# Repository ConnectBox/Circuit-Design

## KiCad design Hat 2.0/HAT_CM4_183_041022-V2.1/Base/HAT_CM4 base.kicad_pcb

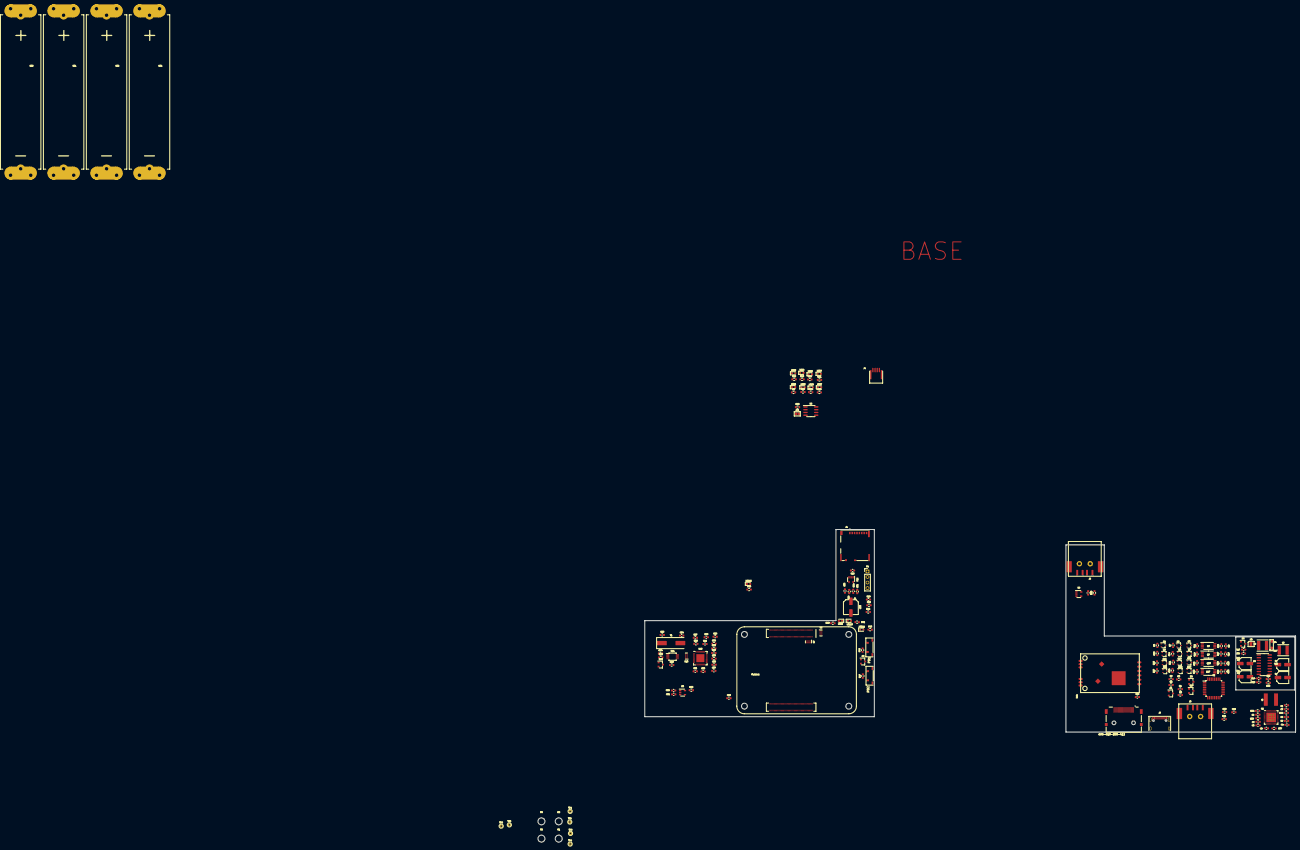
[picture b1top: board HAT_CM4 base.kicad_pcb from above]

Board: 2 copper layers, 299.3 x 93.1 mm, 178 parts (0 on the bottom side), 133 nets, no tracks yet.

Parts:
BT1, BT2, BT3, BT4: Battery Connector; Battery 18650-3
C1, C2, C3, C4, C19, C20, C25, C26, C27, C32, C34, C36, C38: 10uF; C_0603_1608Metric
C5, C6, C7: 4.7uF; C_0603_1608Metric
C8, C9, C18: 1uF; C_0603_1608Metric
C10, C39, C40: 22uF; C_0603_1608Metric
C11, C12, C16, C17: 150uf; CP_Elec_5x3
C13: 1.0uf; C_0603_1608Metric
C14: 0.22uf; C_0603_1608Metric
C15, C21, C22, C28, C29, C31, C33, C35, C37: 0.1uf; C_0603_1608Metric
C23, C24: 9pF; C_0603_1608Metric
C30: 100uF; CP_Elec_6.3x4.5
D1, D2, D3, D5: MMBD914; D_SOT-23_ANK
D4: NRVTS260ESFT1G; SOD-123FL
H1, H2, H3, H4: MountingHole; MountingHole_3.2mm_M3
J1: Micro_SD_Card; SDCARD_MOLEX_503398-1892
J2: 690-019-298-412; HDMI_CnC_SMT
J3, J5: USB_A; USB_A_CUI_smd
J4: Conn_01x04; HFW4R
J6: USB-C; USB-C-GCT
JP1: SolderJumper_2_Open; SolderJumper-2_P1.3mm_Open_TrianglePad1.0x1.5mm
L1: 4.7 uH; INDUCTOR_SMD_6x6-1
L2: 1.0 uH; L_Taiyo-Yuden_MD-5050
L3: 1.5 uH; L_Taiyo-Yuden_NR-50xx
LED1, LED3, LED5, LED7: Blue; LED_0603_1608Metric
LED2, LED4, LED6, LED8, LED9: Red; LED_0603_1608Metric
LED10: Green; LED_0603_1608Metric
LED11: LED Green; LED_0603_1608Metric
LED12: Amber; LED_0603_1608Metric
Module1: ComputeModule4; Raspberry-Pi-4-Compute-Module
P1: Conn_01x04; PinHeader_1x04_P2.54mm_Vertical
PB1, PB2: SPST-PUSH; SW-TL3330A
Q1: NX6008; SOT-23
Q2, Q3, Q4, Q6, Q7, Q8, Q10, Q11, Q12, Q14, Q15, Q16: 3J15; SOT-323_SC-70
Q5, Q9, Q13, Q17: 8205A; TSSOP-8_4.4x3mm_P0.65mm
Q18: 2N7002; SOT-23
R1, R6, R9, R13, R16, R20, R23, R27, R30, R35, R42, R46, R47: 10K; R_0603_1608Metric
R2, R43, R44, R54, R55: 2.2K; R_0603_1608Metric
R3, R4, R11, R18, R25, R33: 20K; R_0603_1608Metric
R5, R10, R14, R17, R21, R24, R28, R32: 100K; R_0603_1608Metric
R7: 36K; R_0603_1608Metric
R8, R12, R15, R19, R22, R26, R29, R31, R48: 510; R_0603_1608Metric
R34: 0.03 ohm; R_0603_1608Metric
R36: 100; R_0603_1608Metric
R37: 200K; R_0603_1608Metric
R38: 1.8K; R_0603_1608Metric
R39: 220K; R_0603_1608Metric
R40: 2.0; R_0603_1608Metric
R41, R45, R51: 1K; R_0603_1608Metric
R49, R52, R59: 12K; R_0603_1608Metric
R50, R53: 51K; R_0603_1608Metric
R56, R57, R58, R60: 36.0K; R_0603_1608Metric
TP1: AC_IN; TestPoint_THTPad_D1.5mm_Drill0.7mm
TP2: Pwr_Gnd; TestPoint_THTPad_D1.5mm_Drill0.7mm
TP3: Bat+; TestPoint_THTPad_D1.5mm_Drill0.7mm
TP4: IPS; TestPoint_THTPad_D1.5mm_Drill0.7mm
TP5: IPS_Sw; TestPoint_THTPad_D1.5mm_Drill0.7mm
TP6: 5V; TestPoint_THTPad_D1.5mm_Drill0.7mm
U1: ATtiny88-AU; TQFP-32_7x7mm_P0.8mm
U2: AXP209; UQFN-48-1EP_6x6mm_Pitch0.4mm_75
U3: AP22814A; U-DFN2020-6
U4: MAX1709ESE; SOP-16_3.9x9.9mm_P1.27mm
U5: AT24CS01-SSHM; SOIC-8_3.9x4.9mm_P1.27mm
U6, U7, U10: TPD4EUSB30; USON-10_2.5x1.0mm_P0.5mm
U8, U9, U12: RT9742ANGJ5F; SOT-23-5
U11: FSUSB42MUX; MSOP-10_3x3mm_P0.5mm
U13: USB2514B-I/M2; QFN-36-1EP_6x6mm_P0.5mm_EP3.7x3.7mm
U14: HC-R8812AF1; HC-R8812AU2
Y1: 24MHz; Crystal_SMD_HC49-SD

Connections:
+3.3v: C18.1, C26.1, C27.1, C28.1, C29.1, C31.1, C33.1, C35.1, C37.1, C40.1, Module1.78 (GPIO_VREF(1.8v/3.3v_Input)), Module1.84 (+3.3v_(Output)), Module1.86 (+3.3v_(Output)), P1.2, R43.2, R44.2, R46.2, R47.2, R48.1, R49.2, R50.1, R53.1, R54.1, U8.5 (VIN), U11.1 (VCC), U13.5 (VDDA33), U13.10 (VDDA33), U13.15 (VDD33), U13.23 (VDD33), U13.27 (VBUS_DET), U13.29 (VDDA33), U13.36 (VDDA33), U14.1 (PDN), U14.2 (3.3V)
+5V: C16.1, C17.1, C21.1, C25.1, D1.2 (A), D4.1 (K), JP1.1 (A), LED11.2 (A), Module1.77 (+5v_(Input)), Module1.79 (+5v_(Input)), Module1.81 (+5v_(Input)), Module1.83 (+5v_(Input)), Module1.85 (+5v_(Input)), Module1.87 (+5v_(Input)), R4.1, R40.1, R41.1, R52.2, TP6.1, U5.8 (VCC), U9.5 (VIN), U12.5 (VIN)
/AC_IN: C39.1, D2.2 (A), J6.A4/B9 (Power), J6.B4/A9 (Power), R1.2, R3.1, TP1.1, U2.32 (AC_IN), U2.33 (AC_IN)
/Batteries/BT1-: BT1.2 (-), Q4.1 (G), Q5.6 (S2), Q5.7 (S2), R7.1, R9.1, R10.2, R12.2
/Batteries/BT2-: BT2.2 (-), Q8.1 (G), Q9.6 (S2), Q9.7 (S2), R16.1, R17.2, R19.2
/Batteries/BT3-: BT3.2 (-), Q12.1 (G), Q13.6 (S2), Q13.7 (S2), R23.1, R24.2, R26.2
/Batteries/BT4-: BT4.2 (-), Q16.1 (G), Q17.6 (S2), Q17.7 (S2), R30.1, R31.2, R32.2
/Battery/ADC2: R1.1, R2.1, U1.25 (PC2)
/Battery/BATT+: BT1.1 (+), BT2.1 (+), BT3.1 (+), BT4.1 (+), C1.1, LED2.1 (K), LED4.1 (K), LED6.1 (K), LED8.1 (K), Q4.2 (S), Q8.2 (S), Q12.2 (S), Q16.2 (S), R5.1, R9.2, R14.1, R16.2, R21.1, R23.2, R28.1, R30.2, R34.1, TP3.1, U2.38 (Batt), U2.39 (Batt), U2.42 (BatSense)
/Battery/BT1_PRES: Q2.2 (S), Q3.2 (S), Q4.3 (D), R6.1, U1.30 (PD0)
/Battery/BT2_PRES: Q6.2 (S), Q7.2 (S), Q8.3 (D), R13.1, U1.31 (PD1)
/Battery/BT3_PRES: Q10.2 (S), Q11.2 (S), Q12.3 (D), R20.1, U1.32 (PD2)
/Battery/BT4_PRES: Q14.2 (S), Q15.2 (S), Q16.3 (D), R27.1, U1.1 (PD3)
/Battery/I2C_SCL: Module1.80 (SCL0), P1.3, R44.1, U1.28 (PC5), U2.2 (SCK), U5.6 (SCL)
/Battery/I2C_SDA: Module1.82 (SDA0), P1.4, R43.1, U1.27 (PC4), U2.1 (SDA), U5.5 (SDA)
/Battery/MISO: Module1.40 (GPIO9), U1.16 (PB4)
/Battery/MOSI: Module1.44 (GPIO10), U1.15 (PB3)
/Battery/SCL: Module1.38 (GPIO11), U1.17 (PB5)
/Battery//BT1_ENA: Q2.1 (G), Q3.1 (G), R7.2, U1.19 (PA0)
/Battery//BT2_ENA: Q6.1 (G), Q7.1 (G), R14.2, U1.22 (PA1)
/Battery//BT3_ENA: Q10.1 (G), Q11.1 (G), R21.2, U1.3 (PA2)
/Battery//BT4_ENA: Q14.1 (G), Q15.1 (G), R28.2, U1.6 (PA3)
/Battery//RESET: Module1.46 (GPIO22), U1.29 (~RESET/PC6)
/CM4_GPIO/+1.8v: Module1.88 (+1.8v_(Output)), Module1.90 (+1.8v_(Output))
/CM4_GPIO/EXT_ENA: D3.2 (A), R50.2, R51.2, U2.20 (EXTEN)
/CM4_GPIO/GPIO6: LED12.1 (K), Module1.30 (GPIO6)
/CM4_GPIO/GPIO_IRQ: C19.1, Module1.51 (GPIO15), R51.1
/CM4_GPIO/GPIO_PB1: D5.2 (A), Module1.56 (GPIO3), R46.1
/CM4_GPIO/GPIO_PB2: Module1.54 (GPIO4), PB2.1, R47.1
/CM4_GPIO/PI_nLED_Activity: Module1.21 (PI_nLED_Activity), R45.1
/CM4_GPIO/PowerSwitch: D5.1 (K), PB1.1, U2.47 (PwrON)
/CM4_GPIO/SD_CLK: J1.5 (CLK), Module1.57 (SD_CLK)
/CM4_GPIO/SD_CMD: J1.3 (CMD), Module1.62 (SD_CMD)
/CM4_GPIO/SD_DAT0: J1.7 (DAT0), Module1.63 (SD_DAT0)
/CM4_GPIO/SD_DAT1: J1.8 (DAT1), Module1.67 (SD_DAT1)
/CM4_GPIO/SD_DAT2: J1.1 (DAT2), Module1.69 (SD_DAT2)
/CM4_GPIO/SD_DAT3: J1.2 (DAT3/CD), Module1.61 (SD_DAT3)
/CM4_GPIO/SD_PWR: C20.1, J1.4 (VDD), U8.1 (VOUT)
/CM4_GPIO/SD_PWR_ON: Module1.75 (SD_PWR_ON), R49.1, U8.4 (EN)
/CM4_GPIO/TRD0_N: Module1.10 (Ethernet_Pair0_N), U7.4 (D2+), U7.7
/CM4_GPIO/TRD0_P: Module1.12 (Ethernet_Pair0_P), U7.5 (D2-), U7.6
/CM4_GPIO/TRD1_N: Module1.6 (Ethernet_Pair1_N), U7.2 (D1-), U7.9
/CM4_GPIO/TRD1_P: Module1.4 (Ethernet_Pair1_P), U7.1 (D1+), U7.10
/CM4_GPIO/TRD2_N: Module1.9 (Ethernet_Pair2_N), U6.4 (D2+), U6.7
/CM4_GPIO/TRD2_P: Module1.11 (Ethernet_Pair2_P), U6.5 (D2-), U6.6
/CM4_GPIO/TRD3_N: Module1.5 (Ethernet_Pair3_N), U6.2 (D1-), U6.9
/CM4_GPIO/TRD3_P: Module1.3 (Ethernet_Pair3_P), U6.1 (D1+), U6.10
/CM4_HighSpeed/HDMI0_CEC: J2.13 (CEC), Module1.151 (HDMI0_CEC)
/CM4_HighSpeed/HDMI0_CK_N: J2.12 (CK-), Module1.190 (HDMI0_CLK_N)
/CM4_HighSpeed/HDMI0_CK_P: J2.10 (CK+), Module1.188 (HDMI0_CLK_P)
/CM4_HighSpeed/HDMI0_D0_N: J2.9 (D0-), Module1.184 (HDMI0_TX0_N)
/CM4_HighSpeed/HDMI0_D0_P: J2.7 (D0+), Module1.182 (HDMI0_TX0_P)
/CM4_HighSpeed/HDMI0_D1_N: J2.6 (D1-), Module1.178 (HDMI0_TX1_N)
/CM4_HighSpeed/HDMI0_D1_P: J2.4 (D1+), Module1.176 (HDMI0_TX1_P)
/CM4_HighSpeed/HDMI0_D2_N: J2.3 (D2-), Module1.172 (HDMI0_TX2_N)
/CM4_HighSpeed/HDMI0_D2_P: J2.1 (D2+), Module1.170 (HDMI0_TX2_P)
/CM4_HighSpeed/HDMI0_HOTPLUG: J2.19 (HPD/HEAC-), Module1.153 (HDMI0_HOTPLUG)
/CM4_HighSpeed/HDMI0_SCL: J2.15 (SCL), Module1.200 (HDMI0_SCL)
/CM4_HighSpeed/HDMI0_SDA: J2.16 (SDA), Module1.199 (HDMI0_SDA)
/CM4_HighSpeed/HDMI_5v: C22.1, J2.18 (+5V), U9.1 (VOUT)
/CM4_HighSpeed/USB2_N: Module1.103 (USB2_N), U11.4 (D_N)
/CM4_HighSpeed/USB2_P: Module1.105 (USB2_P), U11.3 (D_P)
/CM4_HighSpeed/USBOTG_ID: Module1.101 (USB_OTG_ID), Q18.3 (D), R54.2, U11.2 (SEL)
/Charger/IPS_OUT: C3.1, C4.1, R35.2, R38.1, TP4.1, U2.13 (LDO_24_In), U2.21 (APS), U2.34 (IPS_Out), U2.35 (IPS_Out), U2.40 (LDO_3_In), U2.44 (Vin_1), U3.1 (Vin)
/Power/IPS_SW: C11.1, C12.1, L2.1, TP5.1, U3.5 (Vout), U4.1 (ONA)
/USB Hub/HD1_N: J4.2, U10.5 (D2-), U10.6, U13.1 (USBDM_DN1/PRT_DIS_M1)
/USB Hub/HD1_P: J4.3, U10.4 (D2+), U10.7, U13.2 (USBDP_DN1/PRT_DIS_P1)
/USB Hub/HD2_N: U13.3 (USBDM_DN2/PRT_DIS_M2), U14.3 (DM-)
/USB Hub/HD2_P: U13.4 (USBDP_DN2/PRT_DIS_P2), U14.4 (DP+)
/USB Hub/HD3_N: J5.2 (D-), U13.6 (USBDM_DN3/PRT_DIS_M3)
/USB Hub/HD3_P: J5.3 (D+), U13.7 (USBDP_DN3/PRT_DIS_P3)
/USB Hub/HD4_N: J3.2 (D-), U13.8 (USBDM_DN4/PRT_DIS_M4)
/USB Hub/HD4_P: J3.3 (D+), U13.9 (USBDP_DN4/PRT_DIS_P4)
/USB Hub/OTG_D+: J6.A6 (D+), J6.B6 (D+), U10.1 (D1+), U10.10, U11.9 (HSD1_P)
/USB Hub/OTG_D-: J6.A7 (D-), J6.B7 (D-), U10.2 (D1-), U10.9, U11.8 (HSD1_M)
/USB Hub/OTG_ID: J6.A5 (CC1), J6.B5 (CC2), R55.2
/USB Hub/PWR1: U12.4 (EN), U13.12 (PRTPWR1/BC_EN1)
/USB Hub/USBH_N: U11.6 (HSD0_M), U13.30 (USBDM_UP)
/USB Hub/USBH_P: U11.7 (HSD0_P), U13.31 (USBDP_UP)
/USB Hub/VBUS: C30.1, C32.1, C34.1, C36.1, C38.1, J3.1 (VBUS), J4.1, J5.1 (VBUS), U12.1 (VOUT)
/USB Hub/nEXTRST: Module1.100 (nEXTRST), U13.26 (RESET_N)
/USB Hub/nOCS1: U12.3 (/FLG), U13.13 (OCS_N1), U13.17 (OCS_N2), U13.19 (OCS_N3), U13.21 (OCS_N4)
GND: C4.2, C8.1, C9.1, C18.2, C19.2, C20.2, C21.2, C22.2, C23.2, C24.2, C25.2, C26.2, C27.2, C28.2, C29.2, C30.2, C31.2, C32.2, C33.2, C34.2, C35.2, C36.2, C37.2, C38.2, C39.2, C40.2, J1.6 (VSS), J2.2 (D2S), J2.5 (D1S), J2.8 (D0S), J2.11 (CKS), J2.17 (GND), J2.SH1 (SH), J2.SH2 (SH), J2.SH3 (SH), J2.SH4 (SH), J3.4 (GND), J3.5 (Shield), J4.4, J5.4 (GND), J5.5 (Shield), J6.1 (Shell), J6.A1/B12 (GND), J6.B1/A12 (GND), L3.2, Module1.1 (GND), Module1.2 (GND), Module1.7 (GND), Module1.8 (GND), Module1.13 (GND), Module1.14 (GND), Module1.22 (GND), Module1.23 (GND), Module1.32 (GND), Module1.33 (GND), Module1.42 (GND), Module1.43 (GND), Module1.52 (GND), Module1.53 (GND), Module1.59 (GND), Module1.60 (GND), Module1.65 (GND), Module1.66 (GND), Module1.71 (GND), Module1.74 (GND), Module1.98 (GND), Module1.107 (GND), Module1.108 (GND), Module1.113 (GND), Module1.114 (GND), Module1.119 (GND), Module1.120 (GND), Module1.125 (GND), Module1.126 (GND), Module1.131 (GND), Module1.132 (GND), Module1.137 (GND), Module1.138 (GND), Module1.144 (GND), Module1.150 (GND), Module1.155 (GND), Module1.156 (GND), Module1.161 (GND), Module1.162 (GND), Module1.167 (GND), Module1.168 (GND), Module1.173 (GND), Module1.174 (GND), Module1.179 (GND), Module1.180 (GND), Module1.185 (GND), Module1.186 (GND), Module1.191 (GND), Module1.192 (GND), Module1.197 (GND), Module1.198 (GND), P1.1, PB1.2, PB2.2, Q18.2 (S), R37.1, R42.1, R56.2, R57.2, R58.2, R59.1, R60.2, U2.22 (A_Gnd), U5.1 (A0), U5.2 (A1), U5.3 (A2), U5.4 (GND), U6.3 (GND), U6.8 (GND), U7.3 (GND), U7.8 (GND), U8.2 (GND), U9.2 (GND), U10.3 (GND), U10.8 (GND), U11.5 (GND), U11.10 (nOE), U12.2 (GND), U13.37 (VSS), U14.5 (GND), U14.7 (GND), U14.9 (GND), U14.10 (GND), U14.12 (GND), U14.13 (GND), U14.14 (GND), U14.15 (GND)
unnamed: C2.1, L1.1, R34.2, U2.43 (ChgSense)
unnamed: C5.2, U2.12 (LDO_2)
unnamed: C6.2, U2.11 (LDO_4)
unnamed: C7.2, U2.41 (LDO_3)
unnamed: C8.2, U2.26 (V_Internal), U2.27 (LDO_1_Set)
unnamed: C9.2, U2.24 (V_Ref)
unnamed: C10.1, D3.1 (K), R39.1, U3.3 (ENA)
unnamed: C13.1, U4.6 (SS/LIM)
unnamed: C14.1, U4.7 (REF)
unnamed: C15.1, R40.2, U4.9 (OUT), U4.14 (_3.3/5), U4.15 (CLK)
unnamed: C23.1, U13.33 (XTALIN/CLKIN), Y1.1
unnamed: C24.1, U13.32 (XTALOUT), Y1.2
unnamed: D1.1 (K), D2.1 (K), U1.4 (VCC), U1.18 (AVCC)
unnamed: D4.2 (A), L2.2, U4.2 (LX), U4.3 (LX), U4.4 (LX)
unnamed: JP1.2 (B), R42.2, U5.7 (WP)
unnamed: L1.2, U2.45 (LX1)
unnamed: LED1.1 (K), LED3.1 (K), LED5.1 (K), LED7.1 (K), Q1.3 (D), R5.2, U1.5 (GND), U1.21 (GND)
unnamed: LED1.2 (A), R8.2
unnamed: LED2.2 (A), R12.1
unnamed: LED3.2 (A), R15.2
unnamed: LED4.2 (A), R19.1
unnamed: LED5.2 (A), R22.2
unnamed: LED6.2 (A), R26.1
unnamed: LED7.2 (A), R29.2
unnamed: LED8.2 (A), R31.1
unnamed: LED9.1 (K), U2.36 (ChgLED)
unnamed: LED9.2 (A), R38.2
unnamed: LED10.2 (A), R41.2
unnamed: LED11.1 (K), R45.2
unnamed: LED12.2 (A), R48.2
unnamed: Q1.1 (G), R3.2, R4.2
unnamed: Q2.3 (D), Q5.4 (G1), R8.1, R11.1
unnamed: Q3.3 (D), Q5.5 (G2), R10.1
unnamed: Q6.3 (D), Q9.4 (G1), R15.1, R18.1
unnamed: Q7.3 (D), Q9.5 (G2), R17.1
unnamed: Q10.3 (D), Q13.4 (G1), R22.1, R25.1
unnamed: Q11.3 (D), Q13.5 (G2), R24.1
unnamed: Q14.3 (D), Q17.4 (G1), R29.1, R33.1
unnamed: Q15.3 (D), Q17.5 (G2), R32.1
unnamed: Q18.1 (G), R53.2, R55.1
unnamed: R35.1, U2.6 (N_VBus_En)
unnamed: R36.1, U2.37 (TS)
unnamed: R37.2, U2.23 (Bias)
unnamed: R52.1, U9.4 (EN)
unnamed: R56.1, U13.24 (SCL/SMBCLK/CFG_SEL0)
unnamed: R57.1, U13.22 (SDA/SMBDATA/NON_REM1)
unnamed: R58.1, U13.28 (SUSP_IND/LOCAL_PWR/NON_REM0)
unnamed: R59.2, U13.35 (RBIAS)
unnamed: R60.1, U13.25 (HS_IND/CFG_SEL1)
PWR_GND: C1.2, C2.2, C3.2, C5.1, C6.1, C7.1, C10.2, C11.2, C12.2, C13.2, C14.2, C15.2, C16.2, C17.2, L3.1, LED10.1 (K), Q1.2 (S), Q5.2 (S1), Q5.3 (S1), Q9.2 (S1), Q9.3 (S1), Q13.2 (S1), Q13.3 (S1), Q17.2 (S1), Q17.3 (S1), R2.2, R6.2, R11.2, R13.2, R18.2, R20.2, R25.2, R27.2, R33.2, R36.2, R39.2, TP2.1, U2.4 (N_OE), U2.9 (PGnd_2), U2.16 (PGnd_3), U2.46 (PGnd_1), U2.49 (GND_PAD), U3.2 (GND), U4.5 (GND), U4.8 (GND), U4.10 (FB), U4.11 (PGND), U4.12 (PGND), U4.13 (PGND)

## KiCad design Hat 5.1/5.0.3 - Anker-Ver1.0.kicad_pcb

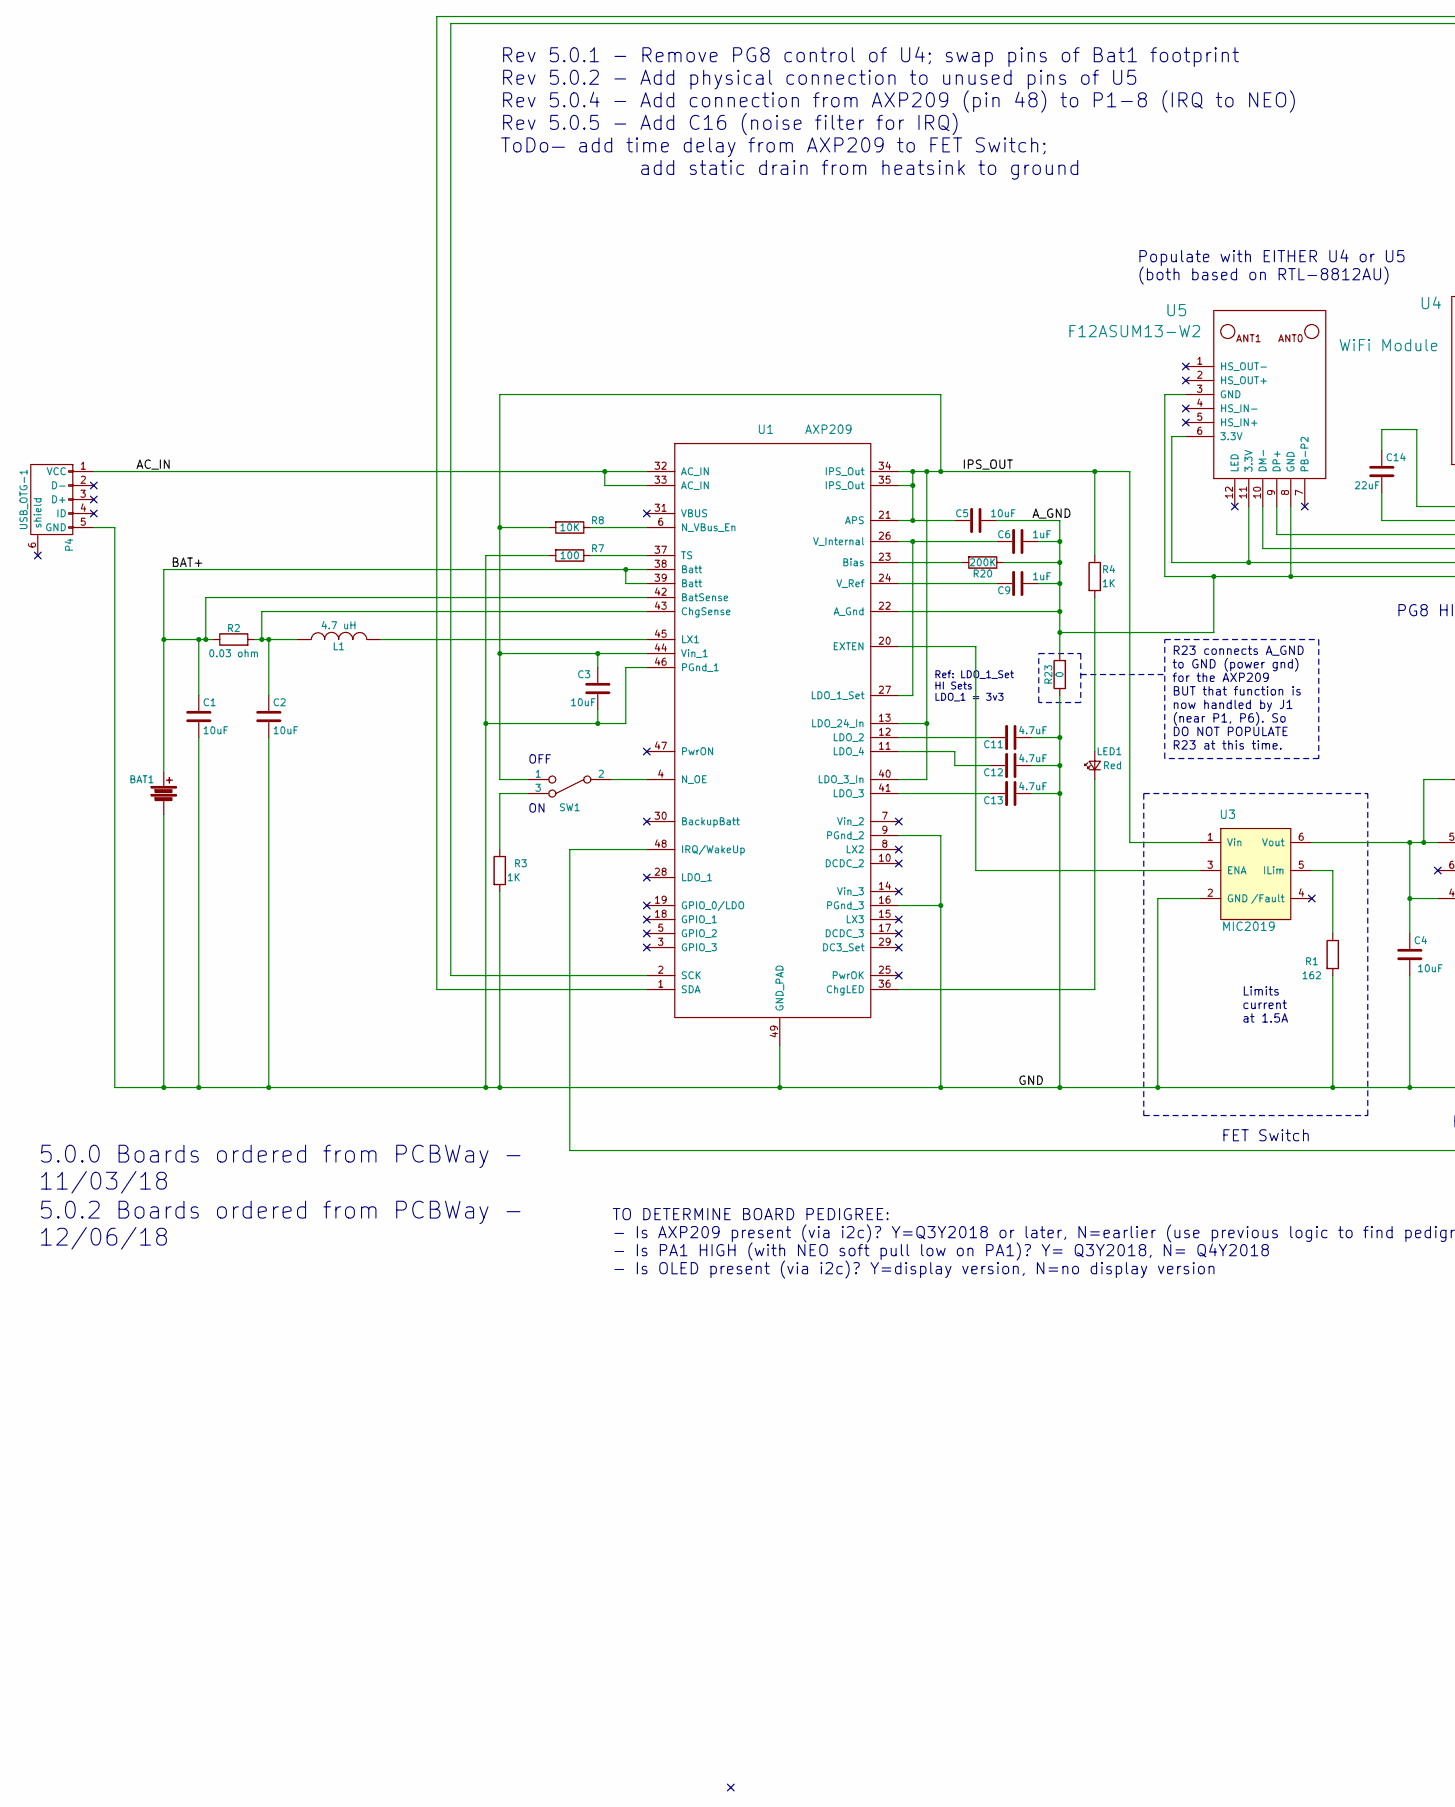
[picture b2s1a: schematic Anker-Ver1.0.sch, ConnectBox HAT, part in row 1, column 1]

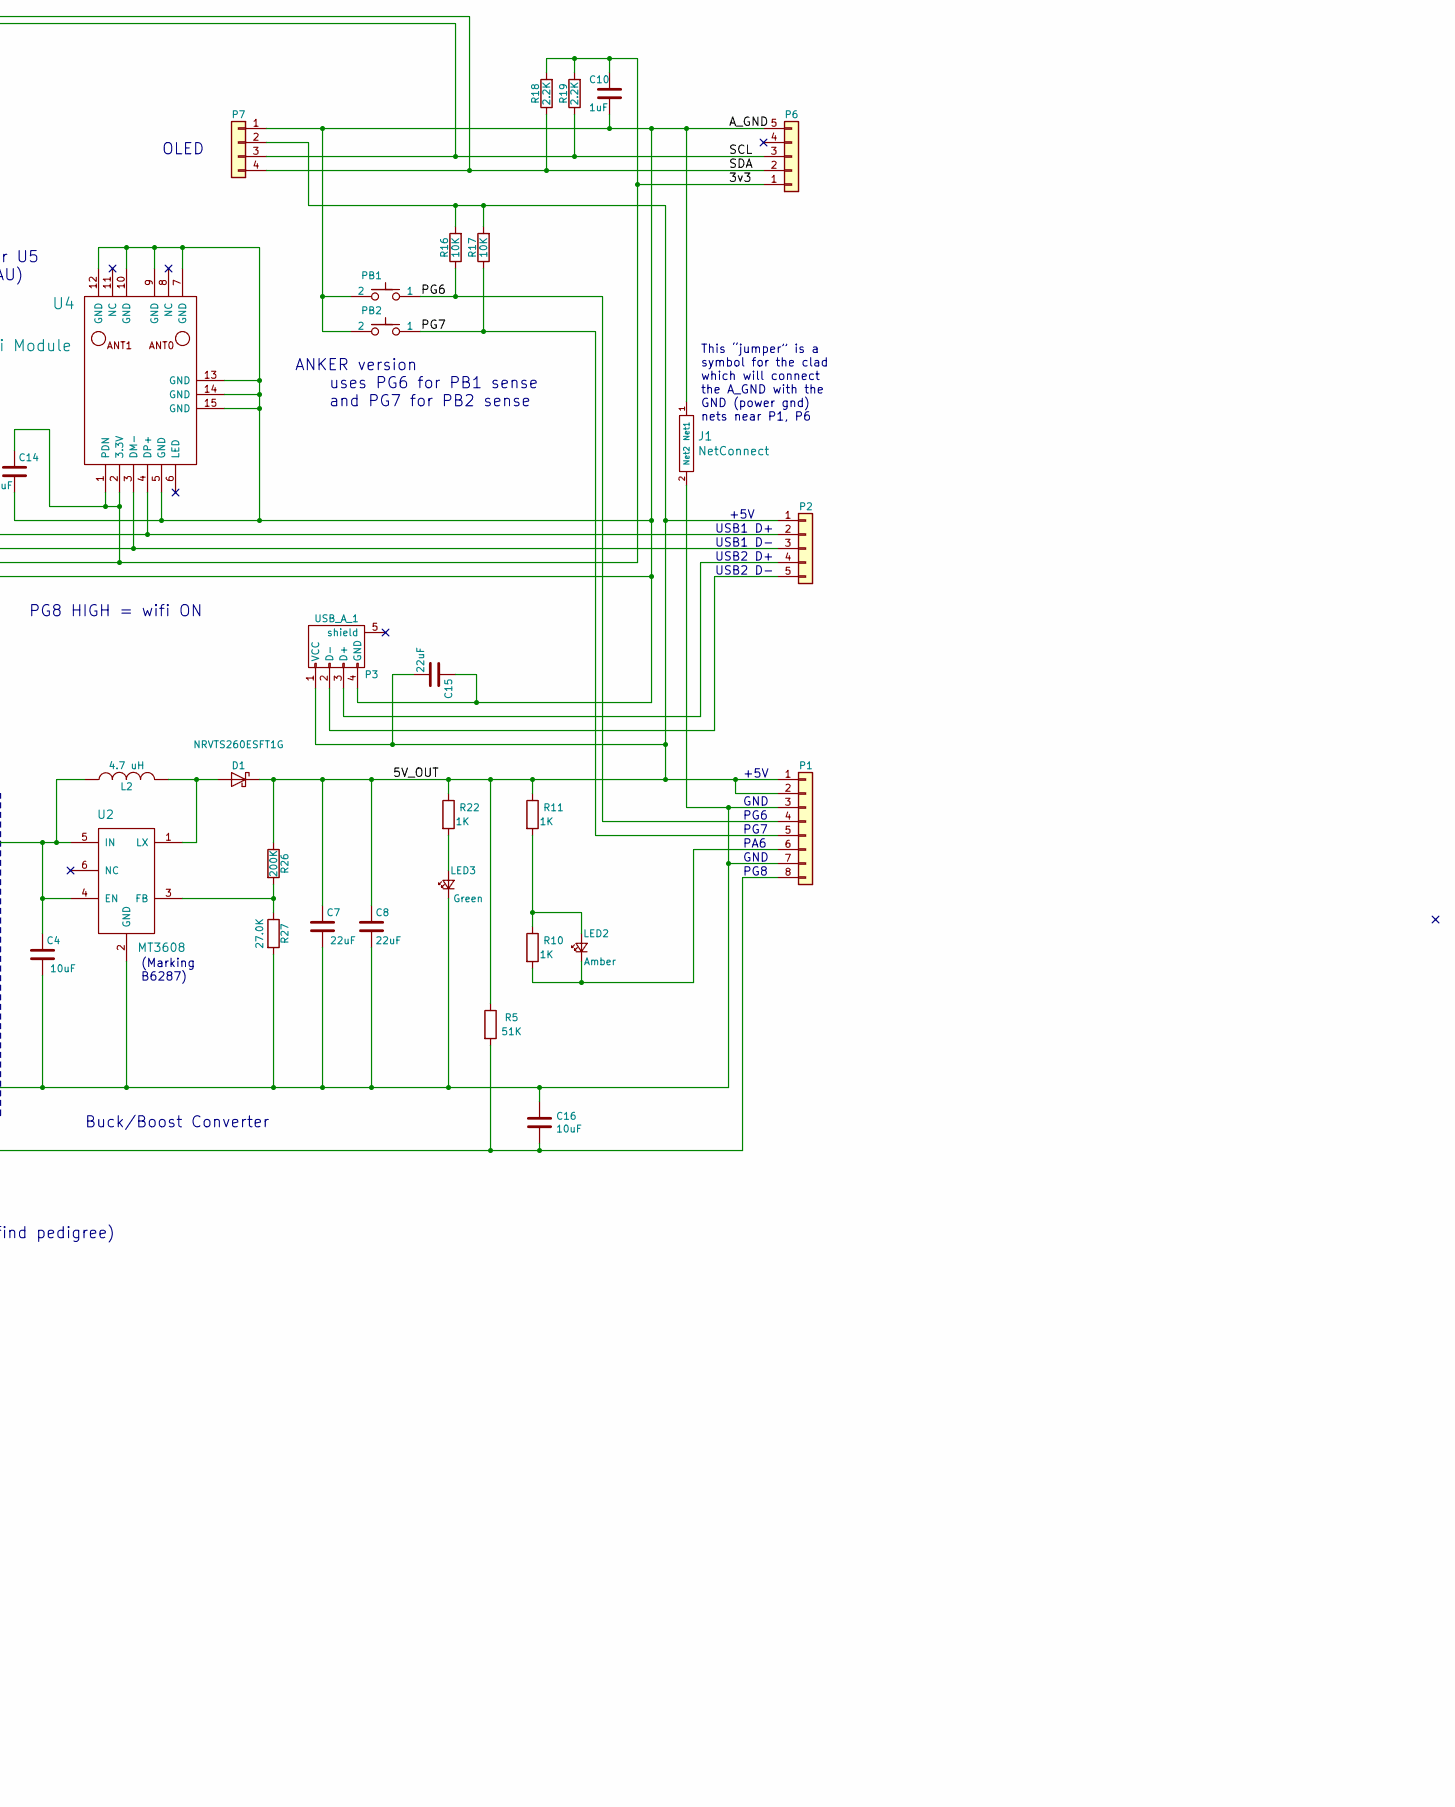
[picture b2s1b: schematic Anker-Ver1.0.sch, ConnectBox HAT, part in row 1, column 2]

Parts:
BAT1: Battery_multi_cell; Molex PicoBlade 53047-0210 - (swapped pins)
C1, C2, C3, C4, C5: 10uF; C_0805; Manufacturer P/N CL21A106MPFNNNE; DigiKey P/N 1276-1144-1-ND
C6, C9, C10: 1uF; C_0805; Manufacturer P/N C0805C105K8PACTU; DigiKey P/N 399-8006-1-ND
C7, C8, C14, C15: 22uF; C_0805; Manufacturer P/N C0805C226M8PAC7800; DigiKey P/N 399-12069-1-ND
C11, C12, C13: 4.7uF; C_0805; Manufacturer P/N CL21B475KPFNNNE; DigiKey P/N 1276-2972-1-ND
C16: 10uF
D1: NRVTS260ESFT1G; SOD-123FL; Manufacturer P/N NRVTS260ESFT1G; DigiKey P/N NRVTS260ESFT1GOSCT-ND
J1: NetConnect
L1, L2: 4.7 uH; INDUCTOR_SMD_6x6-1
LED1: Red; LED_0603; Manufacturer P/N LTST-C191KRKT; DigiKey P/N 160-1447-1-ND
LED2: Amber; LED_0603; Manufacturer P/N LTST-C191KFKT; DigiKey P/N 160-1445-1-ND
LED3: Green; LED_0603; Manufacturer P/N LTST-C191KFKT; DigiKey P/N 160-1446-1-ND
P1: Conn_01x08; PinHeader_1x08_P2.54mm_Vertical
P2, P6: Conn_01x05; PinHeader_1x05_P2.54mm_Vertical
P3: USB_A_1; USB_A
P4: USB_OTG-1; USB_Micro-B_Molex_47346-0001
P7: Conn_01x04; OLED
PB1, PB2: SPST-PUSH; SW-TL3305
R1: 162; R_0805_2012Metric; Manufacturer P/N RC0805FR-07162R; DigiKey P/N 311-162CRCT-ND
R2: 0.03 ohm; R_0805; Manufacturer P/N ERJ-6CWFR030V; DigiKey P/N P19207CT-ND
R3, R4, R10, R11, R22: 1K; R_0805; Manufacturer P/N RC0805FR-071KL; DigiKey P/N 311-1.00KCRCT-ND
R5: 51K; R_0805_2012Metric; Manufacturer P/N RC0805FR-071KL; DigiKey P/N 311-51.0KCRCT-ND
R7: 100; R_0805; Manufacturer P/N RC0805FR-07100RL; DigiKey P/N 311-100CRCT-ND
R8: 10K; R_0805; Manufacturer P/N RC0805FR-0710KL; DigiKey P/N 311-10.0KCRCT-ND
R16, R17: 10K; R_0805; Manufacturer P/N RC0805FR-072K2L; DigiKey P/N 311-2.20KCRCT-ND
R18, R19: 2.2K; R_0805; Manufacturer P/N RC0805FR-072K2L; DigiKey P/N 311-2.20KCRCT-ND
R20, R26: 200K; R_0805; Manufacturer P/N RC0805FR-07200KL; DigiKey P/N 311-200KCRCT-ND
R23: 0; R_0805; Manufacturer P/N RC0805FR-070RL; DigiKey P/N 311-0.0CRCT-ND
R27: 27.0K; R_0805; Manufacturer P/N RC0805FR-0727KL; DigiKey P/N 311-27.0KCRCT-ND
SW1: SPDT-2C; SPDT-OS10211; Manufacturer P/N OS102011MA1QN1; DigiKey P/N CKN9559-ND or CKN9560-ND
U1: AXP209; UQFN-48-1EP_6x6mm_Pitch0.4mm_75; Manufacturer P/N AXP209
U2: MT3608; SOT-23-6a; Manufacturer P/N MT3608
U3: MIC2019; SOT-23-6a; Manufacturer P/N MIC2019YM6-TR; DigiKey P/N 576-2595-1-ND
U4: WiFi Module; HC-R8812AU2
U5: F12ASUM13-W2

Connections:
/3v3: C10.1, C14.1, P6.1, R18.2, R19.2, U4.1 (PDN), U4.2 (3.3V), U5.6 (3.3V), U5.11 (3.3V)
/5V_OUT: C7.1, C8.1, C15.2, D1.1 (K), P1.1, P1.2, P2.1, P3.1 (VCC), P7.2, R5.1, R11.1, R16.2, R17.2, R22.1, R26.1
/AC_IN: P4.1 (VCC), U1.32 (AC_IN), U1.33 (AC_IN)
/A_GND: C5.1, C6.1, C9.1, C10.2, C14.2, C15.1, J1.1 (Net1), P3.4 (GND), P6.5, P7.1, PB1.2, PB2.2, R20.1, R23.2, U1.22 (A_Gnd), U4.5 (GND), U4.7 (GND), U4.9 (GND), U4.10 (GND), U4.12 (GND), U4.13 (GND), U4.14 (GND), U4.15 (GND), U5.3 (GND), U5.8 (GND)
/BAT+: BAT1.1, C1.1, R2.1, U1.38 (Batt), U1.39 (Batt), U1.42 (BatSense)
/GND: BAT1.2, C1.2, C2.2, C3.2, C4.2, C7.2, C8.2, C11.1, C12.1, C13.1, C16.1, J1.2 (Net2), LED3.1 (K), P1.3, P1.7, P4.5 (GND), R1.2, R3.2, R7.2, R23.1, R27.2, U1.9 (PGnd_2), U1.16 (PGnd_3), U1.46 (PGnd_1), U1.49 (GND_PAD), U2.2 (GND), U3.2 (GND)
/IPS_OUT: C3.1, C5.2, R4.1, R8.2, SW1.1, U1.13 (LDO_24_In), U1.21 (APS), U1.34 (IPS_Out), U1.35 (IPS_Out), U1.40 (LDO_3_In), U1.44 (Vin_1), U3.1 (Vin)
/PG6: P1.4, PB1.1, R16.1
/PG7: P1.5, PB2.1, R17.1
/SCL: P6.3, P7.3, R19.1, U1.2 (SCK)
/SDA: P6.2, P7.4, R18.1, U1.1 (SDA)
unnamed: C2.1, L1.1, R2.2, U1.43 (ChgSense)
unnamed: C4.1, L2.1, U2.4 (EN), U2.5 (IN), U3.6 (Vout)
unnamed: C6.2, U1.26 (V_Internal), U1.27 (LDO_1_Set)
unnamed: C9.2, U1.24 (V_Ref)
unnamed: C11.2, U1.12 (LDO_2)
unnamed: C12.2, U1.11 (LDO_4)
unnamed: C13.2, U1.41 (LDO_3)
unnamed: D1.2 (A), L2.2, U2.1 (LX)
unnamed: L1.2, U1.45 (LX1)
unnamed: LED1.1 (K), U1.36 (ChgLED)
unnamed: LED1.2 (A), R4.2
unnamed: LED2.1 (K), P1.6, R10.2
unnamed: LED2.2 (A), R10.1, R11.2
unnamed: LED3.2 (A), R22.2
unnamed: C16.2, P1.8, R5.2, U1.48 (IRQ/WakeUp)
unnamed: P2.2, U4.4 (DP+), U5.9 (DP+)
unnamed: P2.3, U4.3 (DM-), U5.10 (DM-)
unnamed: P2.4, P3.3 (D+)
unnamed: P2.5, P3.2 (D-)
unnamed: R1.1, U3.5 (ILim)
unnamed: R3.1, SW1.3
unnamed: R7.1, U1.37 (TS)
unnamed: R8.1, U1.6 (N_VBus_En)
unnamed: R20.2, U1.23 (Bias)
unnamed: R26.2, R27.1, U2.3 (FB)
unnamed: SW1.2, U1.4 (N_OE)
unnamed: U1.20 (EXTEN), U3.3 (ENA)

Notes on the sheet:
+5V
USB1 D+
USB1 D-
Buck/Boost Converter
PG6
OFF
Ref: LDO_1_Set HI Sets LDO_1 = 3v3
Limits current at 1.5A
(Marking B6287)
FET Switch
PG7
PA6
USB2 D+
USB2 D-
PG8 HIGH = wifi ON
Populate with EITHER U4 or U5 (both based on RTL-8812AU)
GND
PG8
OLED
TO DETERMINE BOARD PEDIGREE: - Is AXP209 present (via i2c)? Y=Q3Y2018 or later, N=earlier (use previous logic to find pedigree) - Is PA1 HIGH (with NEO soft pull low on PA1)? Y= Q3Y2018, N= Q4Y2018 - Is OLED present (via i2c)? Y=display version, N=no display version
ANKER version uses PG6 for PB1 sense and PG7 for PB2 sense
This “jumper” is a symbol for the clad which will connect the A_GND with the GND (power gnd) nets near P1, P6
R23 connects A_GND to GND (power gnd) for the AXP209 BUT that function is now handled by J1 (near P1, P6). So DO NOT POPULATE R23 at this time.
5.0.0 Boards ordered from PCBWay - 11/03/18
Rev 5.0.1 - Remove PG8 control of U4; swap pins of Bat1 footprint Rev 5.0.2 - Add physical connection to unused pins of U5 Rev 5.0.4 - Add connection from AXP209 (pin 48) to P1-8 (IRQ to NEO) Rev 5.0.5 - Add C16 (noise filter for IRQ) ToDo— add time delay from AXP209 to FET Switch; add static drain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
5.0.2 Boards ordered from PCBWay - 12/06/18

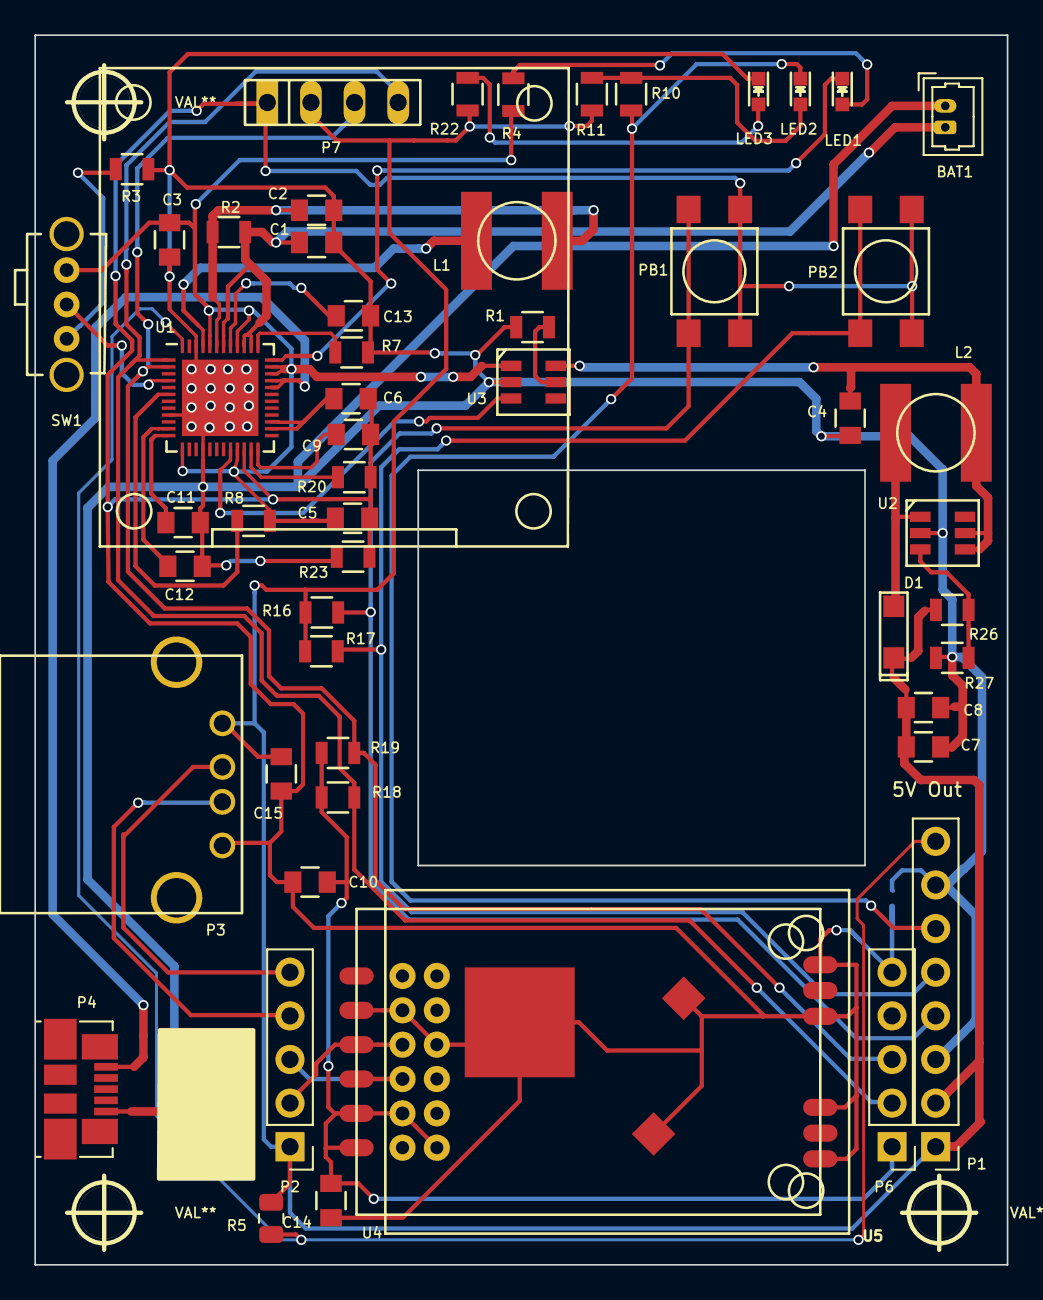
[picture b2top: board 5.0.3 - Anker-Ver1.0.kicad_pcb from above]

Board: 2 copper layers, 56.6 x 71.6 mm, 59 parts (0 on the bottom side), 38 nets.

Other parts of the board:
TP_IPS_OUT1: TestPoint; ProbePad
hole_3mm, hole_3mm#2, hole_3mm#3: VAL**; hole_3mm

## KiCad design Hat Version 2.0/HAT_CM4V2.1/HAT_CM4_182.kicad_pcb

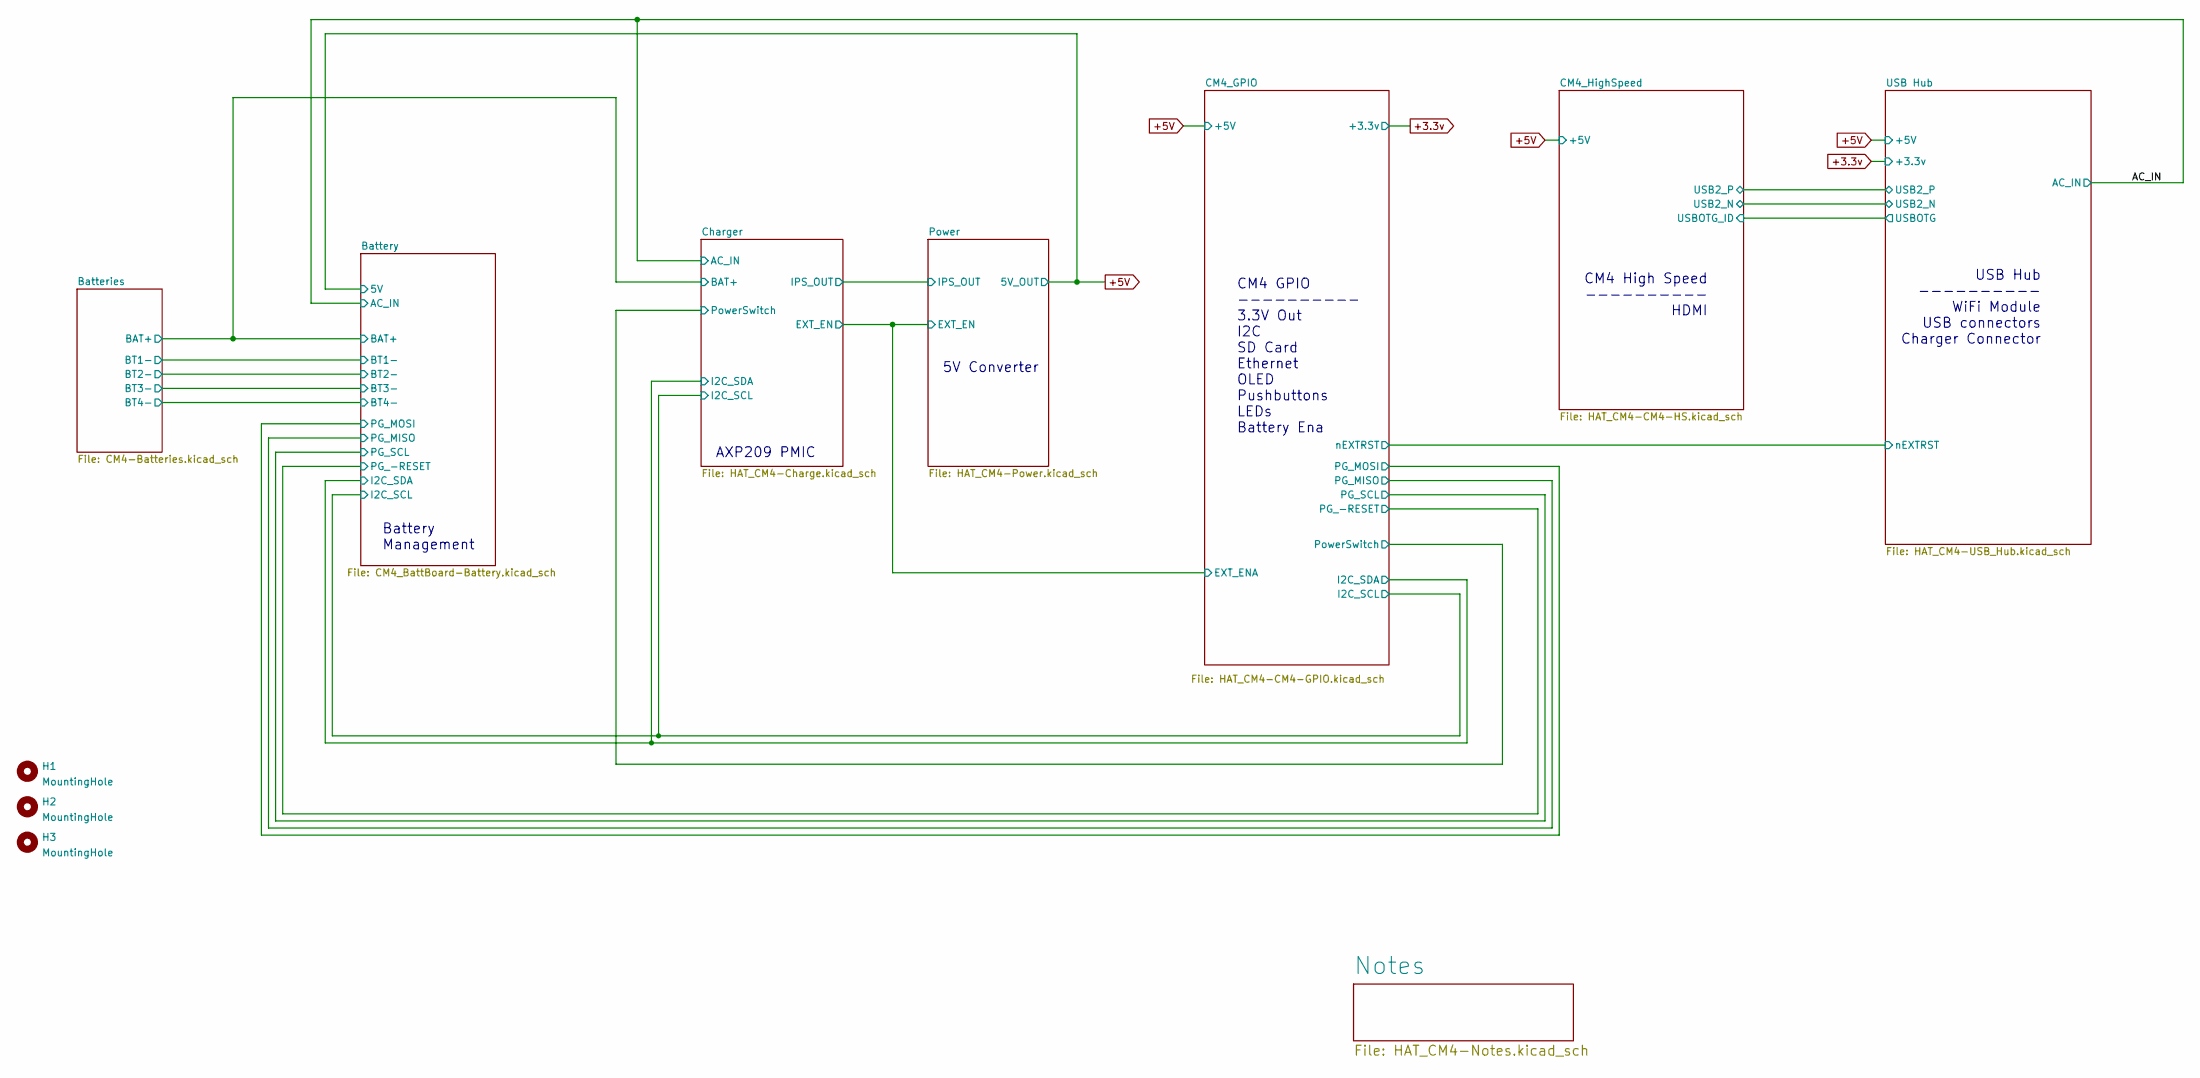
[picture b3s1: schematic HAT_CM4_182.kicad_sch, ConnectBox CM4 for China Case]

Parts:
H1, H2, H3: MountingHole; MountingHole_4.3mm_M4-A

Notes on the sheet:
USB Hub ---------- WiFi Module USB connectors Charger Connector
Battery Management
5V Converter
CM4 GPIO ---------- 3.3V Out I2C SD Card Ethernet OLED Pushbuttons LEDs Battery Ena
CM4 High Speed ---------- HDMI
AXP209 PMIC

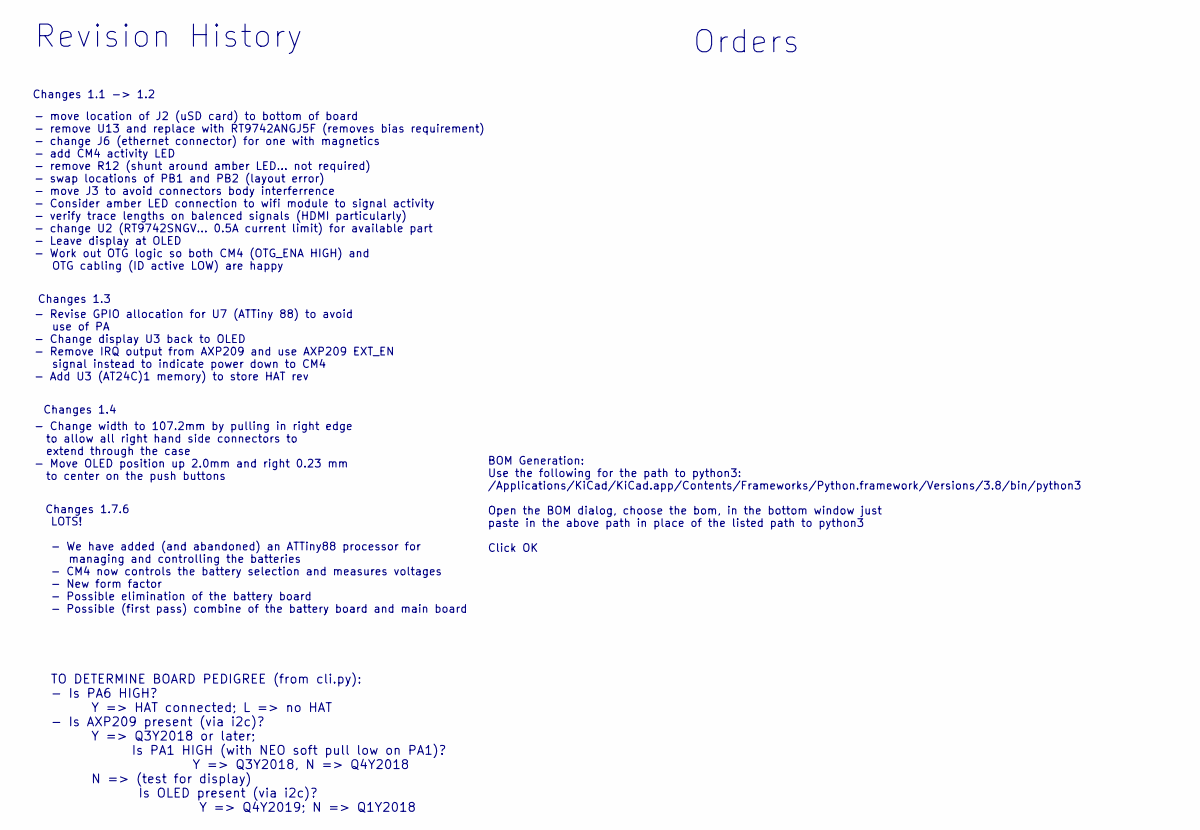
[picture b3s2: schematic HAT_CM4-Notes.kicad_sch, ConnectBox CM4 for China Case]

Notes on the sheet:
Changes 1.7.6
Orders
Changes 1.3
BOM Generation: Use the following for the path to python3: /Applications/KiCad/KiCad.app/Contents/Frameworks/Python.framework/Versions/3.8/bin/python3 Open the BOM dialog, choose the bom, in the bottom window just paste in the above path in place of the listed path to python3 Click OK
- move location of J2 (uSD card) to bottom of board - remove U13 and replace with RT9742ANGJ5F (removes bias requirement) - change J6 (ethernet connector) for one with magnetics - add CM4 activity LED - remove R12 (shunt around amber LED... not required) - swap locations of PB1 and PB2 (layout erro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
TO DETERMINE BOARD PEDIGREE (from cli.py): - Is PA6 HIGH? Y => HAT connected; L => no HAT - Is AXP209 present (via i2c)? Y => Q3Y2018 or later; Is PA1 HIGH (with NEO soft pull low on PA1)? Y => Q3Y2018, N => Q4Y2018 N => (test for display) Is OLED present (via i2c)? Y => Q4Y2019; N => Q1Y2018
LOTS! - We have added (and abandoned) an ATTiny88 processor for managing and controlling the batteries - CM4 now controls the battery selection and measures voltages - New form factor - Possible elimination of the battery board - Possible (first pass) combine of the battery board and main board
Changes 1.4
Changes 1.1 -> 1.2
Revision History
- Change width to 107.2mm by pulling in right edge to allow all right hand side connectors to extend through the case - Move OLED position up 2.0mm and right 0.23 mm to center on the push buttons
- Revise GPIO allocation for U7 (ATTiny 88) to avoid use of PA - Change display U3 back to OLED - Remove IRQ output from AXP209 and use AXP209 EXT_EN signal instead to indicate power down to CM4 - Add U3 (AT24C)1 memory) to store HAT rev

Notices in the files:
Hat 5.1/5.0.3 - Anker-Ver1.0.kicad_pcb:
Copyright 2018
Hat Version 2.0/HAT_CM4V2.1/HAT_CM4_182.kicad_pcb:
ConnectBox RPi (c)2022
(c) 2022
